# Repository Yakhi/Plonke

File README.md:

# Plonke
 One of the keyboards of all time

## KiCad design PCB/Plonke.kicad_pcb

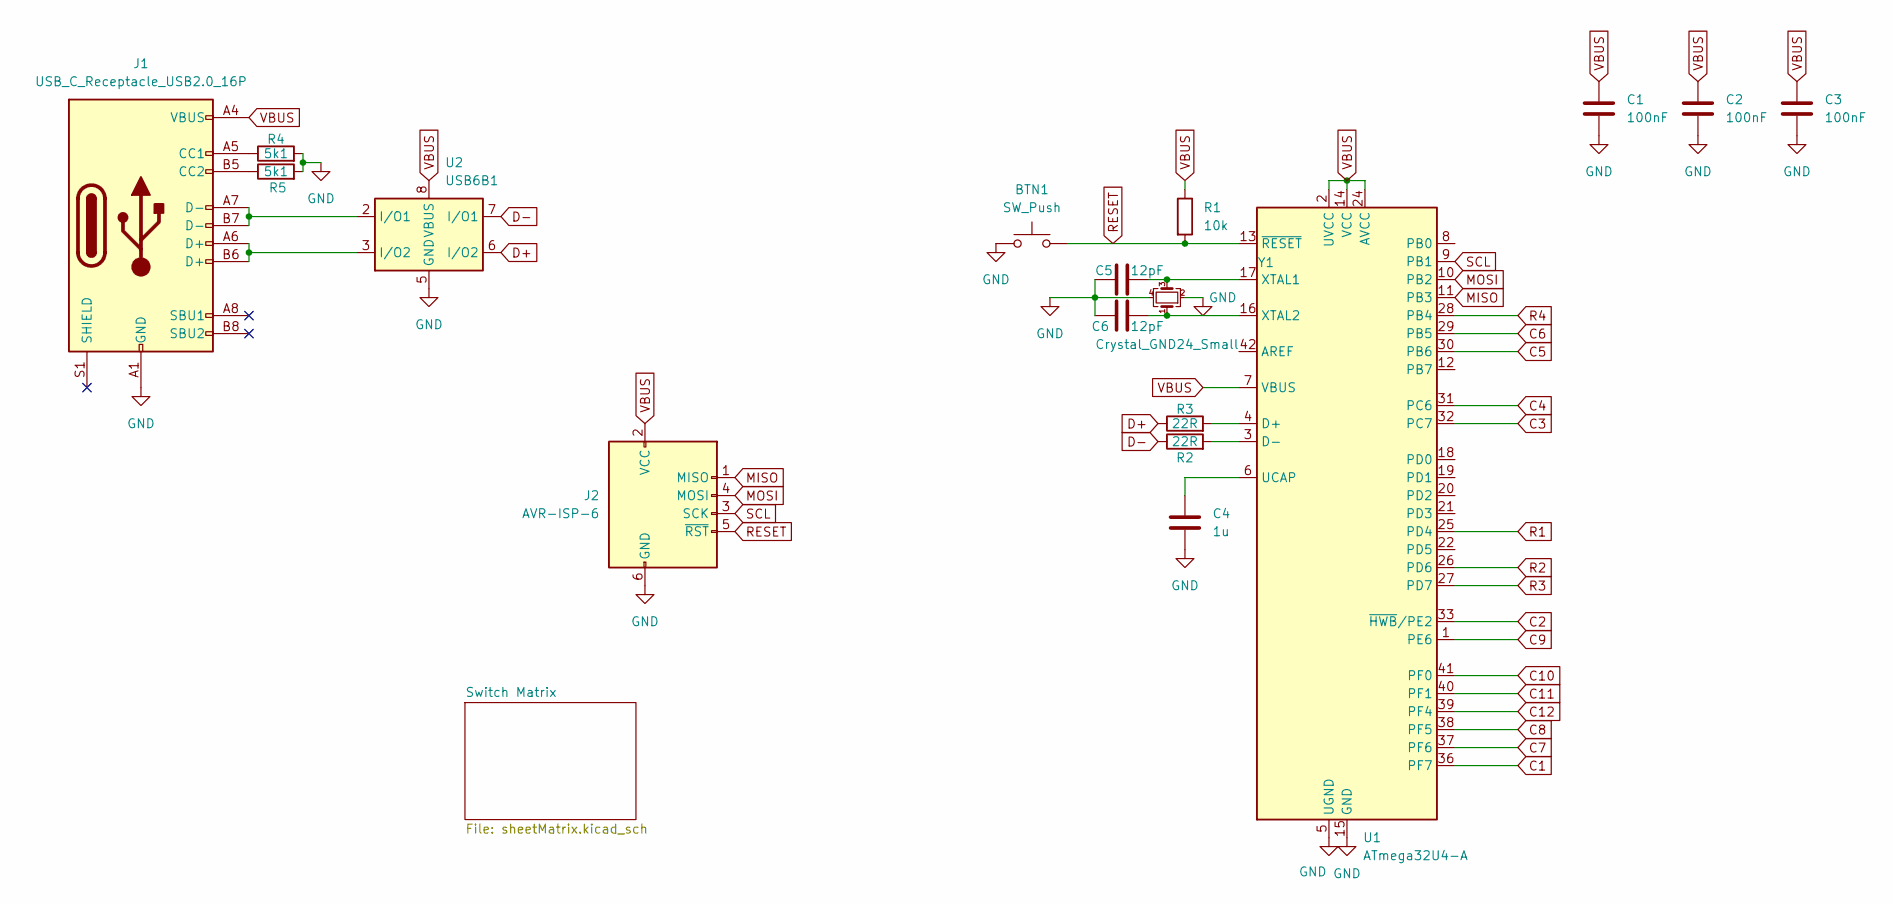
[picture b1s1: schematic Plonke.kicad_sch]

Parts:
BTN1: SW_Push; SW_PUSH_6mm
C1, C2, C3: 100nF; C_Disc_D4.7mm_W2.5mm_P5.00mm
C4: 1u; C_Disc_D4.7mm_W2.5mm_P5.00mm
C5, C6: 12pF; C_Disc_D4.7mm_W2.5mm_P5.00mm
J1: USB_C_Receptacle_USB2.0_16P; USB_C_Receptacle_XKB_U262-16XN-4BVC11
J2: AVR-ISP-6; PinHeader_2x03_P2.54mm_Horizontal
R1: 10k; R_Axial_DIN0207_L6.3mm_D2.5mm_P10.16mm_Horizontal
R2, R3: 22R; R_Axial_DIN0207_L6.3mm_D2.5mm_P10.16mm_Horizontal
R4, R5: 5k1; R_Axial_DIN0207_L6.3mm_D2.5mm_P10.16mm_Horizontal
U1: ATmega32U4-A; TQFP-44_10x10mm_P0.8mm
U2: USB6B1; SOIC-8_3.9x4.9mm_P1.27mm
Y1: Crystal_GND24_Small; Crystal_HC18-U_Vertical

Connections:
C1: U1.36 (PF7); also elsewhere on the board
C2: U1.33 (~HWB/PE2); also elsewhere on the board
C3: U1.32 (PC7); also elsewhere on the board
C4: U1.31 (PC6); also elsewhere on the board
C5: U1.30 (PB6); also elsewhere on the board
C6: U1.29 (PB5); also elsewhere on the board
C7: U1.37 (PF6); also elsewhere on the board
C8: U1.38 (PF5); also elsewhere on the board
C9: U1.1 (PE6); also elsewhere on the board
C10: U1.41 (PF0); also elsewhere on the board
C11: U1.40 (PF1); also elsewhere on the board
C12: U1.39 (PF4); also elsewhere on the board
D+: R3.1, U2.6 (I/O2)
D-: R2.1, U2.7 (I/O1)
GND: BTN1.1, C1.2, C2.2, C3.2, C4.2, C5.1, C6.1, J1.A1 (GND), J1.A12 (GND), J1.B1 (GND), J1.B12 (GND), J2.6 (GND), R4.2, R5.2, U1.5 (UGND), U1.15 (GND), U1.23 (GND), U1.35 (GND), U1.43 (GND), U2.4 (GND), U2.5 (GND), Y1.2, Y1.4
MISO: J2.1 (MISO), U1.11 (PB3)
MOSI: J2.4 (MOSI), U1.10 (PB2)
unnamed: J1.A5 (CC1), R4.1
unnamed: J1.B5 (CC2), R5.1
unnamed: J1.A6 (D+), J1.B6 (D+), U2.3 (I/O2)
unnamed: J1.A7 (D-), J1.B7 (D-), U2.2 (I/O1)
unnamed: R3.2, U1.4 (D+)
unnamed: R2.2, U1.3 (D-)
unnamed: C4.1, U1.6 (UCAP)
unnamed: C5.2, U1.17 (XTAL1), Y1.3
unnamed: C6.2, U1.16 (XTAL2), Y1.1
R1: U1.25 (PD4); also elsewhere on the board
R2: U1.26 (PD6); also elsewhere on the board
R3: U1.27 (PD7); also elsewhere on the board
R4: U1.28 (PB4); also elsewhere on the board
RESET: BTN1.2, J2.5 (~RST), R1.2, U1.13 (~RESET)
SCL: J2.3 (SCK), U1.9 (PB1)
VBUS: C1.1, C2.1, C3.1, J1.A4 (VBUS), J1.A9 (VBUS), J1.B4 (VBUS), J1.B9 (VBUS), J2.2 (VCC), R1.1, U1.2 (UVCC), U1.7 (VBUS), U1.14 (VCC), U1.24 (AVCC), U1.34 (VCC), U1.44 (AVCC), U2.1 (VBUS), U2.8 (VBUS)

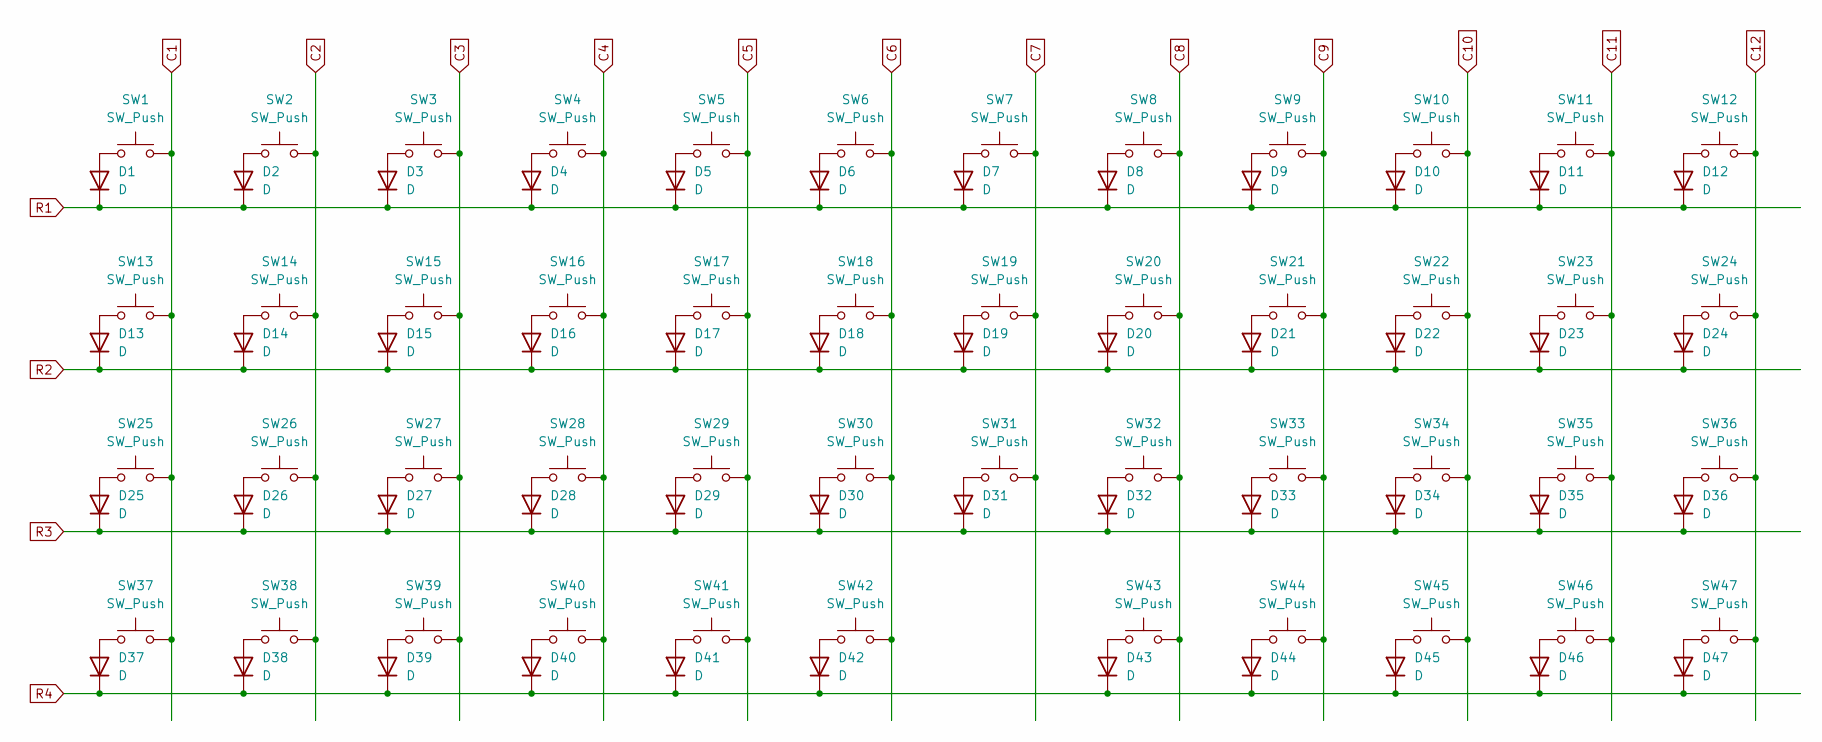
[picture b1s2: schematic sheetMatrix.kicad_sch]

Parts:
D1, D2, D3, D4, D5, D6, D7, D8, D9, D10, D11, D12, D13, D14, D15, D16, D17, D18, D19, D20, D21, D22, D23, D24, D25, D26, D27, D28, D29, D30, D31, D32, D33, D34, D35, D36, D37, D38, D39, D40, D41, D42, D43, D44, D45, D46, D47: D; D_A-405_P7.62mm_Horizontal
SW1, SW2, SW3, SW4, SW5, SW6, SW7, SW8, SW9, SW10, SW11, SW12, SW13, SW14, SW15, SW16, SW17, SW18, SW19, SW20, SW21, SW22, SW23, SW24, SW25, SW26, SW27, SW28, SW29, SW30, SW31, SW32, SW33, SW34, SW35, SW36, SW37, SW38, SW39, SW40, SW41, SW43, SW44, SW45, SW46, SW47: SW_Push; MX-Hotswap-1U
SW42: SW_Push; MX-Hotswap-2U

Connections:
C1: SW1.2, SW13.2, SW25.2, SW37.2; also elsewhere on the board
C2: SW2.2, SW14.2, SW26.2, SW38.2; also elsewhere on the board
C3: SW3.2, SW15.2, SW27.2, SW39.2; also elsewhere on the board
C4: SW4.2, SW16.2, SW28.2, SW40.2; also elsewhere on the board
C5: SW5.2, SW17.2, SW29.2, SW41.2; also elsewhere on the board
C6: SW6.2, SW18.2, SW30.2, SW42.2; also elsewhere on the board
C7: SW7.2, SW19.2, SW31.2; also elsewhere on the board
C8: SW8.2, SW20.2, SW32.2, SW43.2; also elsewhere on the board
C9: SW9.2, SW21.2, SW33.2, SW44.2; also elsewhere on the board
C10: SW10.2, SW22.2, SW34.2, SW45.2; also elsewhere on the board
C11: SW11.2, SW23.2, SW35.2, SW46.2; also elsewhere on the board
C12: SW12.2, SW24.2, SW36.2, SW47.2; also elsewhere on the board
unnamed: D1.2 (A), SW1.1
unnamed: D2.2 (A), SW2.1
unnamed: D3.2 (A), SW3.1
unnamed: D4.2 (A), SW4.1
unnamed: D5.2 (A), SW5.1
unnamed: D6.2 (A), SW6.1
unnamed: D7.2 (A), SW7.1
unnamed: D8.2 (A), SW8.1
unnamed: D9.2 (A), SW9.1
unnamed: D10.2 (A), SW10.1
unnamed: D11.2 (A), SW11.1
unnamed: D12.2 (A), SW12.1
unnamed: D13.2 (A), SW13.1
unnamed: D14.2 (A), SW14.1
unnamed: D15.2 (A), SW15.1
unnamed: D16.2 (A), SW16.1
unnamed: D17.2 (A), SW17.1
unnamed: D18.2 (A), SW18.1
unnamed: D19.2 (A), SW19.1
unnamed: D20.2 (A), SW20.1
unnamed: D21.2 (A), SW21.1
unnamed: D22.2 (A), SW22.1
unnamed: D23.2 (A), SW23.1
unnamed: D24.2 (A), SW24.1
unnamed: D25.2 (A), SW25.1
unnamed: D26.2 (A), SW26.1
unnamed: D27.2 (A), SW27.1
unnamed: D28.2 (A), SW28.1
unnamed: D29.2 (A), SW29.1
unnamed: D30.2 (A), SW30.1
unnamed: D31.2 (A), SW31.1
unnamed: D32.2 (A), SW32.1
unnamed: D33.2 (A), SW33.1
unnamed: D34.2 (A), SW34.1
unnamed: D35.2 (A), SW35.1
unnamed: D36.2 (A), SW36.1
unnamed: D37.2 (A), SW37.1
unnamed: D38.2 (A), SW38.1
unnamed: D39.2 (A), SW39.1
unnamed: D40.2 (A), SW40.1
unnamed: D41.2 (A), SW41.1
unnamed: D42.2 (A), SW42.1
unnamed: D43.2 (A), SW43.1
unnamed: D44.2 (A), SW44.1
unnamed: D45.2 (A), SW45.1
unnamed: D46.2 (A), SW46.1
unnamed: D47.2 (A), SW47.1
R1: D1.1 (K), D2.1 (K), D3.1 (K), D4.1 (K), D5.1 (K), D6.1 (K), D7.1 (K), D8.1 (K), D9.1 (K), D10.1 (K), D11.1 (K), D12.1 (K); also elsewhere on the board
R2: D13.1 (K), D14.1 (K), D15.1 (K), D16.1 (K), D17.1 (K), D18.1 (K), D19.1 (K), D20.1 (K), D21.1 (K), D22.1 (K), D23.1 (K), D24.1 (K); also elsewhere on the board
R3: D25.1 (K), D26.1 (K), D27.1 (K), D28.1 (K), D29.1 (K), D30.1 (K), D31.1 (K), D32.1 (K), D33.1 (K), D34.1 (K), D35.1 (K), D36.1 (K); also elsewhere on the board
R4: D37.1 (K), D38.1 (K), D39.1 (K), D40.1 (K), D41.1 (K), D42.1 (K), D43.1 (K), D44.1 (K), D45.1 (K), D46.1 (K), D47.1 (K); also elsewhere on the board

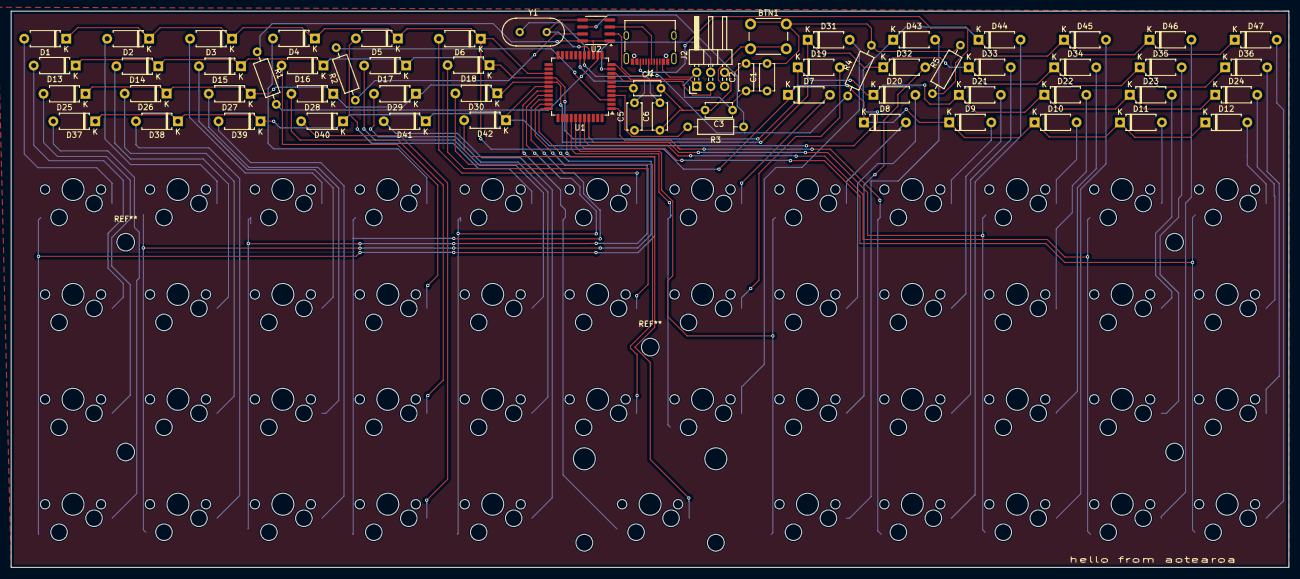
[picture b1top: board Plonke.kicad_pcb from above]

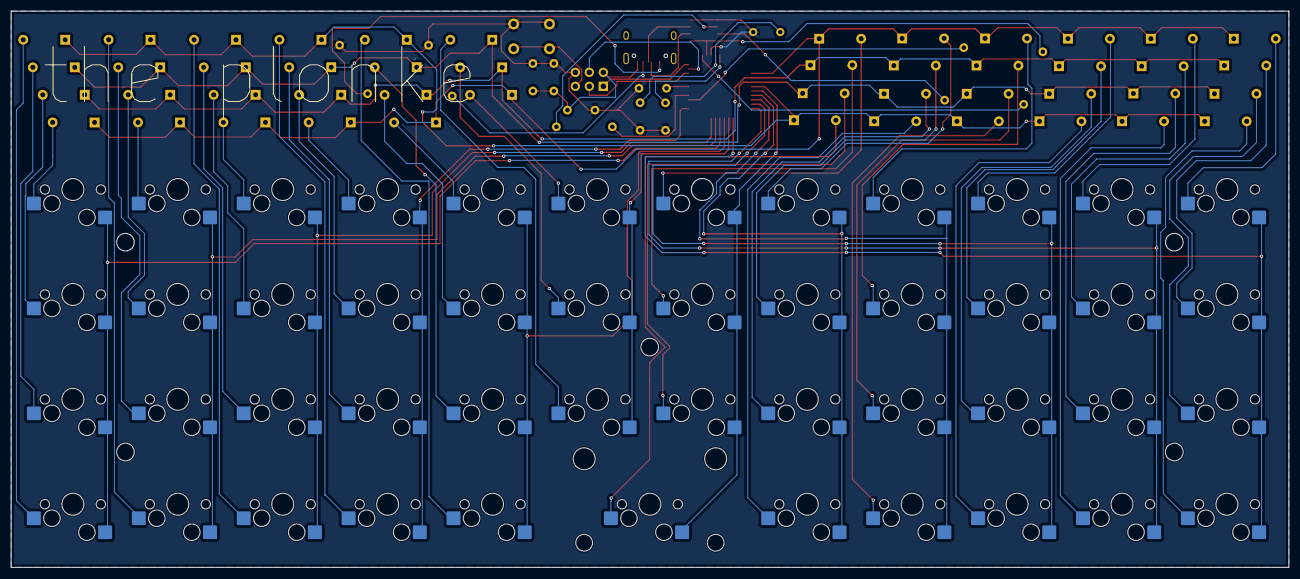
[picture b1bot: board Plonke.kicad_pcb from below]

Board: 2 copper layers, 232.0 x 101.0 mm, 111 parts (47 on the bottom side), 80 nets.

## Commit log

2025-03-10 Setup
    Current PCB Files
2025-03-10 Unpacked downloads....
2025-03-12 Unpack + Parts Markdown File
2025-03-12 Banishing .ds_store
2025-03-12 maybe fixed this time
2025-06-10 ok i'm going to finish this now
    if going 4layer makes this easier i will do it. just one more layer bro, just one more....
2025-06-10 Delete .DS_Store
    they just needed to go...
2025-06-13 Spooky Commit
    Hand Routed Traces
2025-06-13 Take a gander
    nearly there...
2025-06-13 Rows+Col Wired
    now comes the worst part
2025-06-13 final update for the night
2025-06-14 WIRING DONE
    lfg
2025-06-21 ok actually finally wired now
    i forgot to connect the col's together
    classic mistake but with some creative wiring i got there eventually.
2025-06-28 chop and change
    needs drc next
2025-06-30 i have no idea what i'm doing
    please help me (drc)
    why must you hate my diode footprints i don't know what i'm doing plea s leav me aloneeeeeeee
